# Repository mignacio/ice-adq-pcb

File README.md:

# ice-adq-pcb

This printed circuit board is a Shield or Poncho for the EDU-CIAA board.
It is a datalogger for internal combustion engines, it has three digital thermocouple readout sensor.
One variable reluctance RPM sensor.
One Narrowband Lambda probe analog interface.
And a resistive oil pressure sensor analog interface.
It trasmits data over bluetooth via an HM-10 BLE module.

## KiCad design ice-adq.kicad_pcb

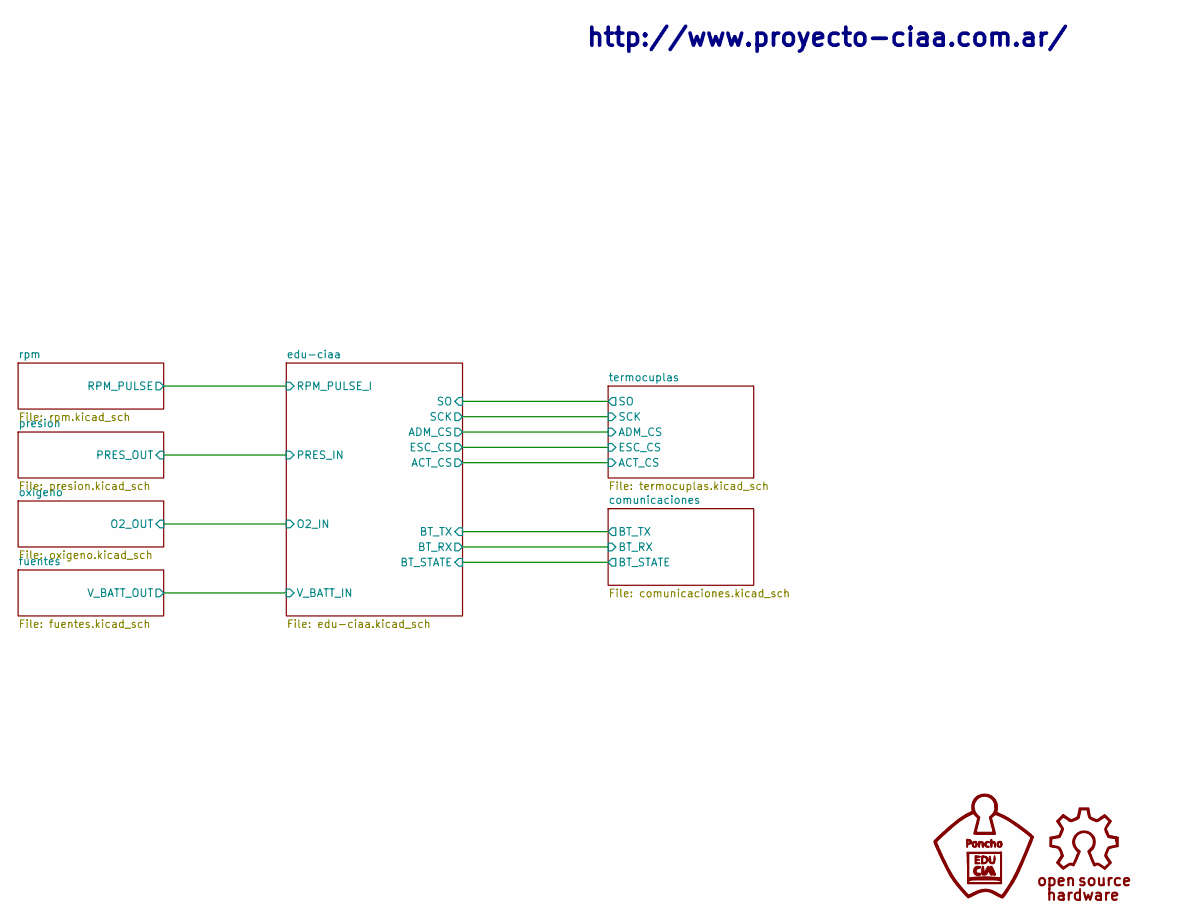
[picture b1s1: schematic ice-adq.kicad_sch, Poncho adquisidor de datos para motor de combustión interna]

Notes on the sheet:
http://www.proyecto-ciaa.com.ar/

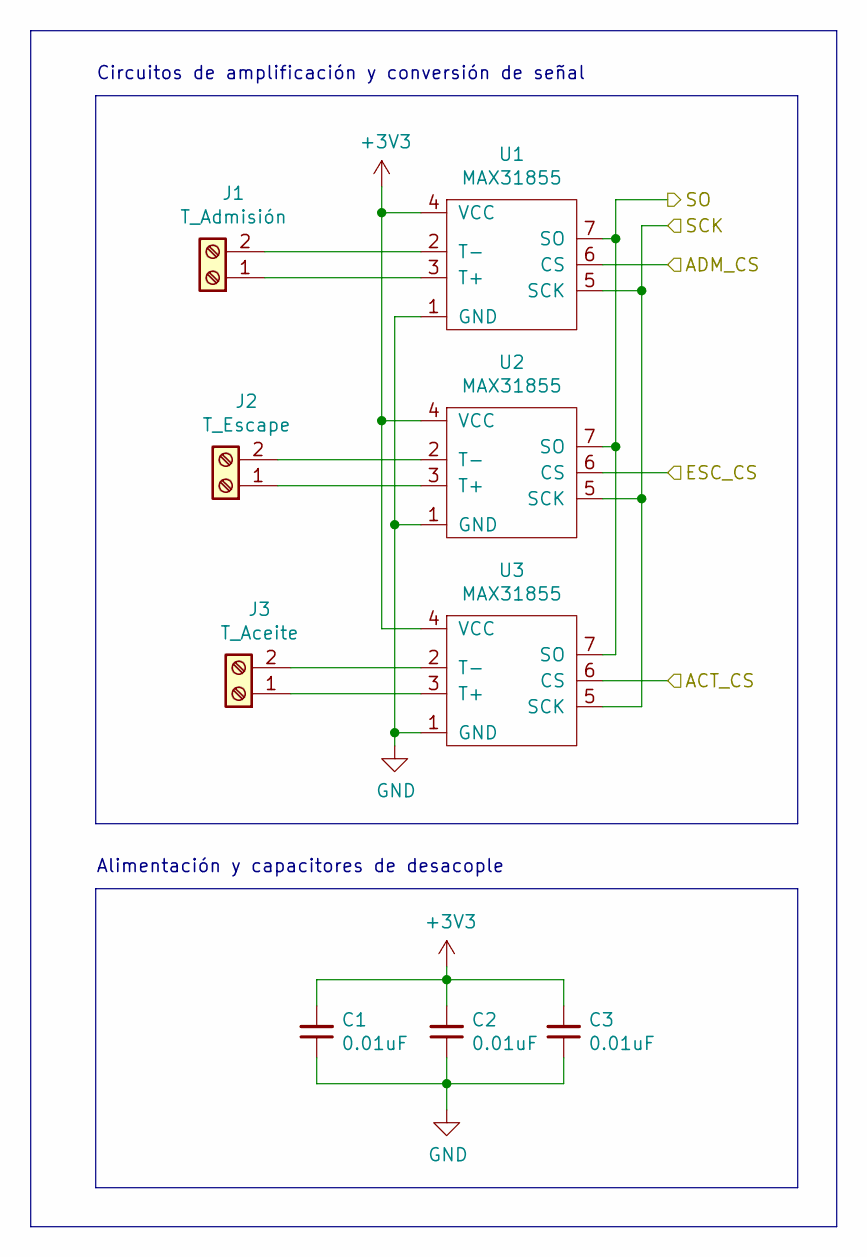
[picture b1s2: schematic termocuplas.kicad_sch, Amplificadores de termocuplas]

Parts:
C1, C2, C3: 0.01uF; C_0805_2012Metric_Pad1.15x1.40mm_HandSolder
J1: T_Admisión; TerminalBlock_bornier-2_P5.08mm
J2: T_Escape; TerminalBlock_bornier-2_P5.08mm
J3: T_Aceite; TerminalBlock_bornier-2_P5.08mm
U1, U2, U3: MAX31855; SOIC-8_3.9x4.9mm_P1.27mm

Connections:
/edu-ciaa/ACT_CS: U3.6 (CS); also elsewhere on the board
/edu-ciaa/ADM_CS: U1.6 (CS); also elsewhere on the board
/edu-ciaa/ESC_CS: U2.6 (CS); also elsewhere on the board
/edu-ciaa/SCK: U1.5 (SCK), U2.5 (SCK), U3.5 (SCK); also elsewhere on the board
/edu-ciaa/SO: U1.7 (SO), U2.7 (SO), U3.7 (SO); also elsewhere on the board
GND: C1.1, C2.1, C3.1, U1.1 (GND), U2.1 (GND), U3.1 (GND); also elsewhere on the board
unnamed: J1.1, U1.3 (T+)
unnamed: J1.2, U1.2 (T-)
unnamed: J2.1, U2.3 (T+)
unnamed: J2.2, U2.2 (T-)
unnamed: J3.1, U3.3 (T+)
unnamed: J3.2, U3.2 (T-)

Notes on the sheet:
Circuitos de amplificación y conversión de señal
Alimentación y capacitores de desacople

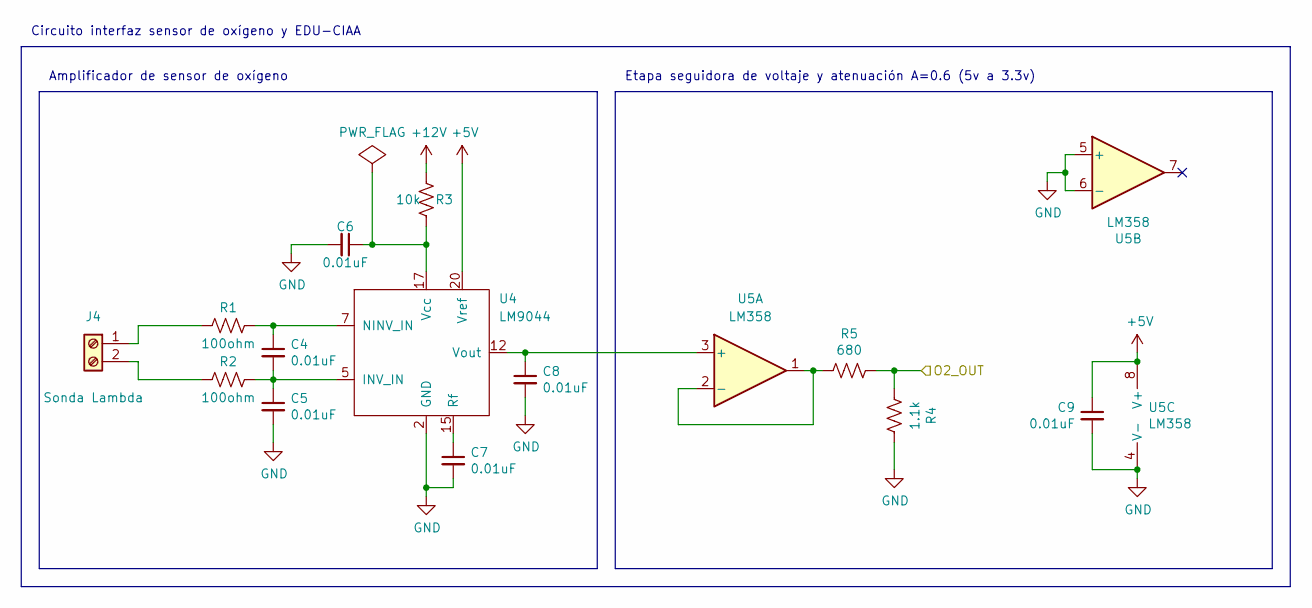
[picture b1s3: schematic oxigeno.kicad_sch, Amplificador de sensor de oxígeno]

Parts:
C4, C5, C6, C7, C8, C9: 0.01uF; C_0805_2012Metric_Pad1.15x1.40mm_HandSolder
J4: Sonda Lambda; TerminalBlock_bornier-2_P5.08mm
R1, R2: 100ohm; R_0805_2012Metric_Pad1.15x1.40mm_HandSolder
R3: 10k; R_0805_2012Metric_Pad1.15x1.40mm_HandSolder
R4: 1.1k; R_0805_2012Metric_Pad1.15x1.40mm_HandSolder
R5: 680; R_0805_2012Metric_Pad1.15x1.40mm_HandSolder
U4: LM9044; PLCC-20
U5: LM358; SOIC-8_3.9x4.9mm_P1.27mm

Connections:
+5V: C9.1, U4.20 (Vref), U5.8 (V+); also elsewhere on the board
+12V: R3.2; also elsewhere on the board
/edu-ciaa/O2_IN: R4.2, R5.1; also elsewhere on the board
GND: C5.2, C6.2, C7.2, C8.2, C9.2, R4.1, U4.2 (GND), U5.4 (V-), U5.5 (+), U5.6 (-); also elsewhere on the board
unnamed: C4.1, R1.1, U4.7 (NINV_IN)
unnamed: C4.2, C5.1, R2.1, U4.5 (INV_IN)
unnamed: C6.1, R3.1, U4.17 (Vcc)
unnamed: C7.1, U4.15 (Rf)
unnamed: C8.1, U4.12 (Vout), U5.3 (+)
unnamed: J4.1, R1.2
unnamed: J4.2, R2.2
unnamed: R5.2, U5.1, U5.2 (-)

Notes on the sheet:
Etapa seguidora de voltaje y atenuación A=0.6 (5v a 3.3v)
Amplificador de sensor de oxígeno
Circuito interfaz sensor de oxígeno y EDU-CIAA

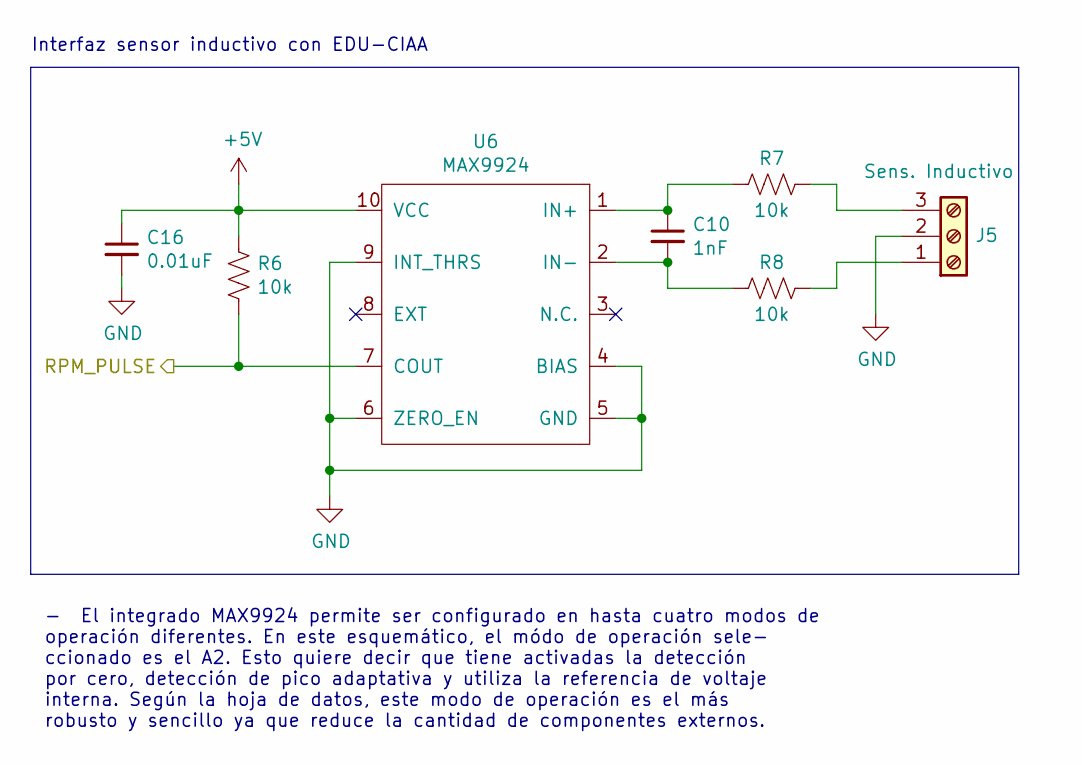
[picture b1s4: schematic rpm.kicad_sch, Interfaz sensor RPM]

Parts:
C10: 1nF; C_0805_2012Metric_Pad1.15x1.40mm_HandSolder
C16: 0.01uF; C_0805_2012Metric_Pad1.15x1.40mm_HandSolder
J5: Sens. Inductivo; TerminalBlock_bornier-3_P5.08mm
R6, R7, R8: 10k; R_0805_2012Metric_Pad1.15x1.40mm_HandSolder
U6: MAX9924; UMAX10

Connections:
+5V: C16.1, R6.1, U6.10 (VCC); also elsewhere on the board
/rpm/RPM_PULSE: R6.2, U6.7 (COUT); also elsewhere on the board
GND: C16.2, J5.2, U6.4 (BIAS), U6.5 (GND), U6.6 (ZERO_EN), U6.9 (INT_THRS); also elsewhere on the board
unnamed: C10.1, R7.2, U6.1 (IN+)
unnamed: C10.2, R8.2, U6.2 (IN-)
unnamed: J5.1, R8.1
unnamed: J5.3, R7.1

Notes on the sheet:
- El integrado MAX9924 permite ser configurado en hasta cuatro modos de operación diferentes. En este esquemático, el módo de operación sele- ccionado es el A2. Esto quiere decir que tiene activadas la detección por cero, detección de pico adaptativa y utiliza la referencia de voltaje interna. Segú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
Interfaz sensor inductivo con EDU-CIAA

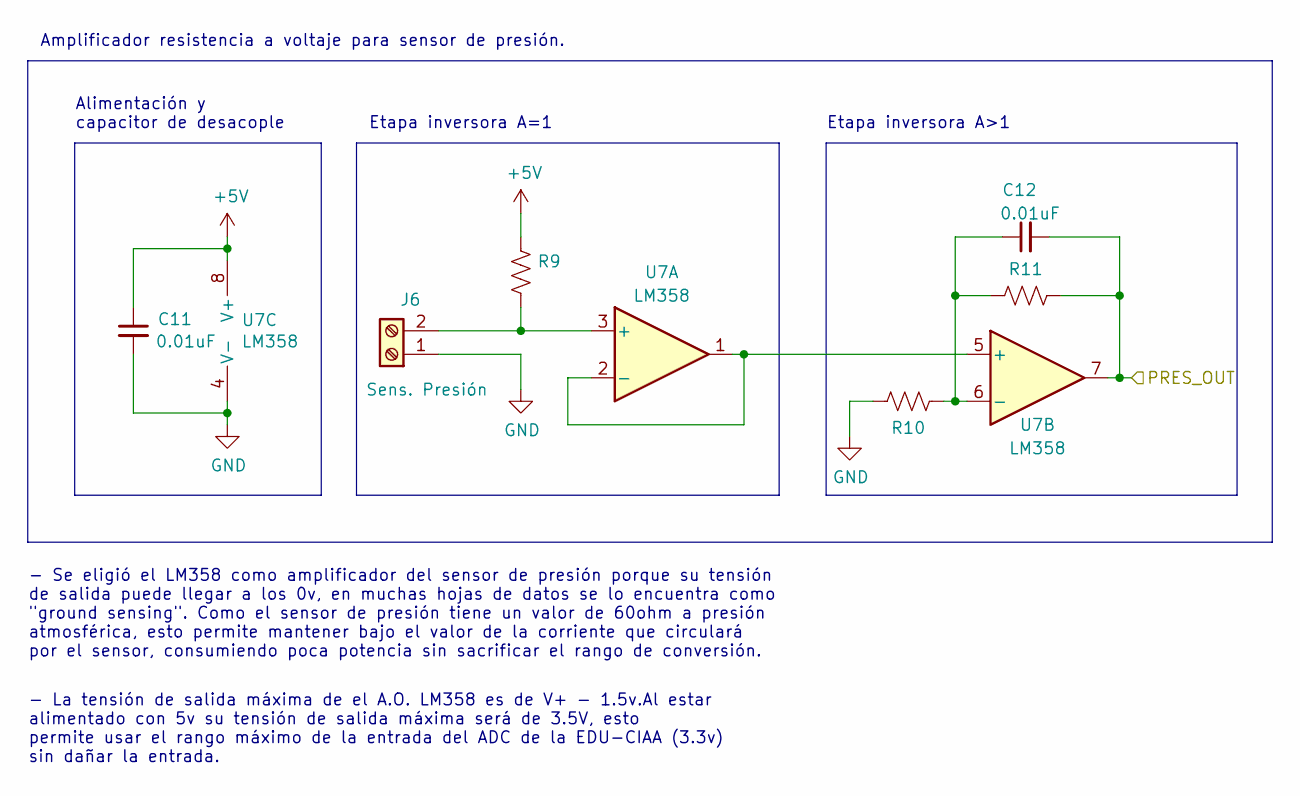
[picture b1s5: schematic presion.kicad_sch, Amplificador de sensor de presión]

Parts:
C11, C12: 0.01uF; C_0805_2012Metric_Pad1.15x1.40mm_HandSolder
J6: Sens. Presión; TerminalBlock_bornier-2_P5.08mm
R9, R10, R11: R_US; R_0805_2012Metric_Pad1.15x1.40mm_HandSolder
U7: LM358; SOIC-8_3.9x4.9mm_P1.27mm

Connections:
+5V: C11.1, R9.1, U7.8 (V+); also elsewhere on the board
/edu-ciaa/PRES_IN: C12.2, R11.1, U7.7; also elsewhere on the board
GND: C11.2, J6.1, R10.1, U7.4 (V-); also elsewhere on the board
unnamed: C12.1, R10.2, R11.2, U7.6 (-)
unnamed: J6.2, R9.2, U7.3 (+)
unnamed: U7.1, U7.2 (-), U7.5 (+)

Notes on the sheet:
Etapa inversora A>1
Amplificador resistencia a voltaje para sensor de presión.
Etapa inversora A=1
- Se eligió el LM358 como amplificador del sensor de presión porque su tensión de salida puede llegar a los 0v, en muchas hojas de datos se lo encuentra como "ground sensing". Como el sensor de presión tiene un valor de 60ohm a presión atmosférica, esto permite mantener bajo el valor de la corrient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
- La tensión de salida máxima de el A.O. LM358 es de V+ - 1.5v.Al estar alimentado con 5v su tensión de salida máxima será de 3.5V, esto permite usar el rango máximo de la entrada del ADC de la EDU-CIAA (3.3v) sin dañar la entrada.
Alimentación y capacitor de desacople

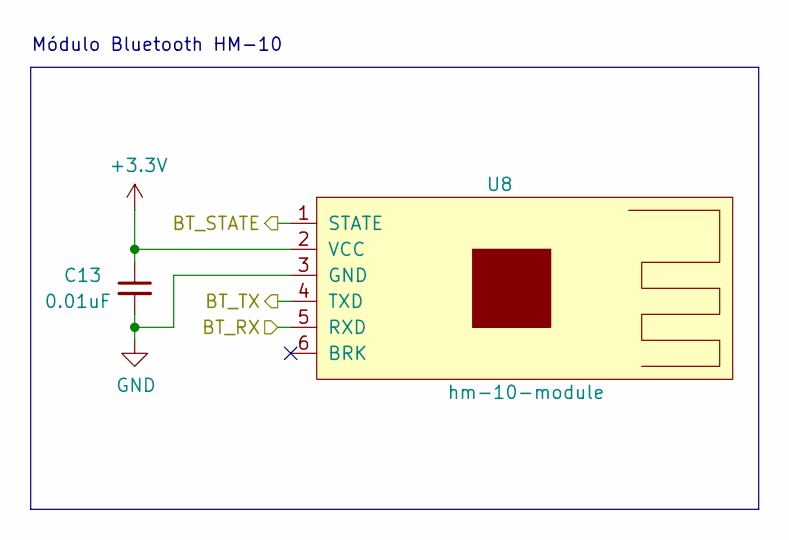
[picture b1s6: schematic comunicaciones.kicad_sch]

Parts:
C13: 0.01uF; C_0805_2012Metric_Pad1.15x1.40mm_HandSolder
U8: hm-10-module

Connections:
/comunicaciones/BT_RX: U8.5 (RXD); also elsewhere on the board
/comunicaciones/BT_STATE: U8.1 (STATE); also elsewhere on the board
/comunicaciones/BT_TX: U8.4 (TXD); also elsewhere on the board
GND: C13.2, U8.3 (GND); also elsewhere on the board

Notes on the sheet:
Módulo Bluetooth HM-10

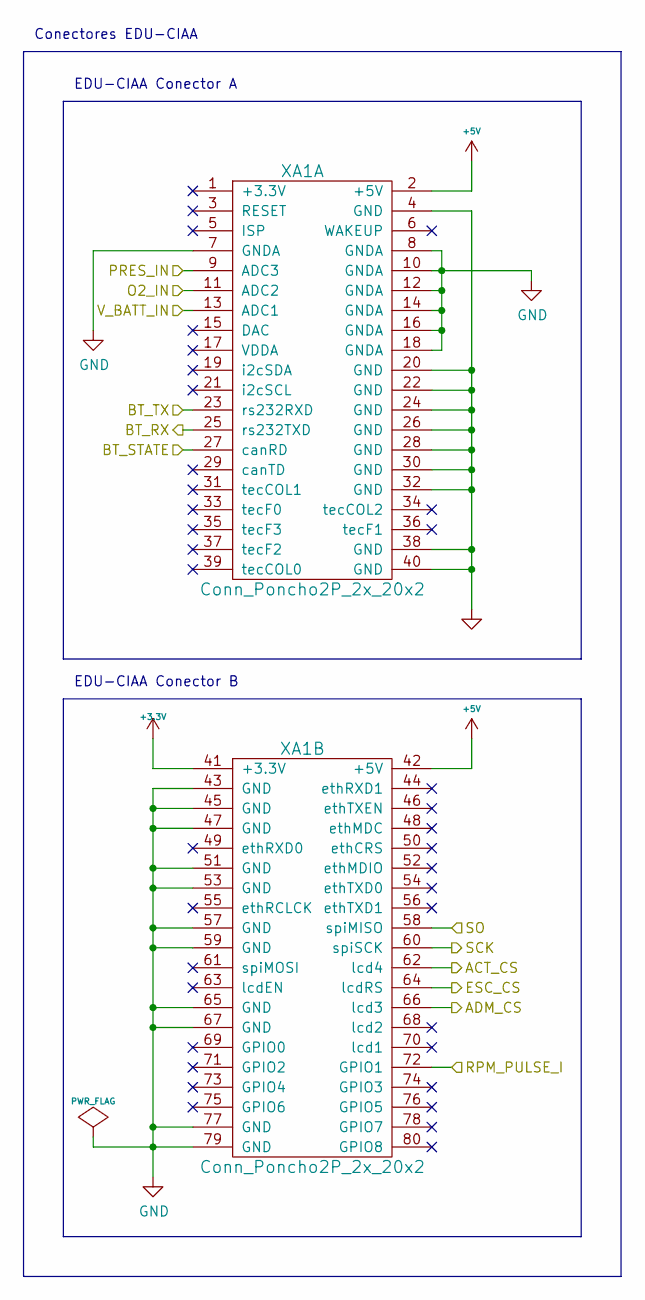
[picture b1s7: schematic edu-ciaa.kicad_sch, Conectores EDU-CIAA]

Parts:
XA1: Conn_Poncho2P_2x_20x2; Conn_Poncho_SinBorde; Digikey# 952-1387-ND

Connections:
+5V: XA1.2 (+5V), XA1.42 (+5V); also elsewhere on the board
/comunicaciones/BT_RX: XA1.25 (rs232TXD); also elsewhere on the board
/comunicaciones/BT_STATE: XA1.27 (canRD); also elsewhere on the board
/comunicaciones/BT_TX: XA1.23 (rs232RXD); also elsewhere on the board
/edu-ciaa/ACT_CS: XA1.62 (lcd4); also elsewhere on the board
/edu-ciaa/ADM_CS: XA1.66 (lcd3); also elsewhere on the board
/edu-ciaa/ESC_CS: XA1.64 (lcdRS); also elsewhere on the board
/edu-ciaa/O2_IN: XA1.11 (ADC2); also elsewhere on the board
/edu-ciaa/PRES_IN: XA1.9 (ADC3); also elsewhere on the board
/edu-ciaa/SCK: XA1.60 (spiSCK); also elsewhere on the board
/edu-ciaa/SO: XA1.58 (spiMISO); also elsewhere on the board
/edu-ciaa/V_BATT_IN: XA1.13 (ADC1); also elsewhere on the board
/rpm/RPM_PULSE: XA1.72 (GPIO1); also elsewhere on the board
GND: XA1.4 (GND), XA1.7 (GNDA), XA1.8 (GNDA), XA1.10 (GNDA), XA1.12 (GNDA), XA1.14 (GNDA), XA1.16 (GNDA), XA1.18 (GNDA), XA1.20 (GND), XA1.22 (GND), XA1.24 (GND), XA1.26 (GND), XA1.28 (GND), XA1.30 (GND), XA1.32 (GND), XA1.38 (GND), XA1.40 (GND), XA1.43 (GND), XA1.45 (GND), XA1.47 (GND), XA1.51 (GND), XA1.53 (GND), XA1.57 (GND), XA1.59 (GND), XA1.65 (GND), XA1.67 (GND), XA1.77 (GND), XA1.79 (GND); also elsewhere on the board

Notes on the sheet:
EDU-CIAA Conector A
EDU-CIAA Conector B
Conectores EDU-CIAA

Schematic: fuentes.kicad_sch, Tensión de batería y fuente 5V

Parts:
C14: 0.22uF; C_0805_2012Metric_Pad1.15x1.40mm_HandSolder
C15, C17, C18: 0.01uF; C_0805_2012Metric_Pad1.15x1.40mm_HandSolder
J7: BATT; TerminalBlock_bornier-2_P5.08mm
R12: 39k; R_0805_2012Metric_Pad1.15x1.40mm_HandSolder
R13: 10k; R_0805_2012Metric_Pad1.15x1.40mm_HandSolder
U9: L7805; TO-263-3_TabPin2
U10: LM358; SOIC-8_3.9x4.9mm_P1.27mm

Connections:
+5V: C15.1, C17.1, U9.3 (OUT), U10.8 (V+); also elsewhere on the board
+12V: C14.1, J7.1, R12.1, U9.1 (IN); also elsewhere on the board
/edu-ciaa/V_BATT_IN: U10.1, U10.2 (-); also elsewhere on the board
GND: C14.2, C15.2, C17.2, C18.2, J7.2, R13.2, U9.2 (GND), U10.4 (V-), U10.5 (+), U10.6 (-); also elsewhere on the board
unnamed: C18.1, R12.2, R13.1, U10.3 (+)

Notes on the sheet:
Conector batería y fuente 5 voltios.
Interfaz tensión de batería y ADC

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
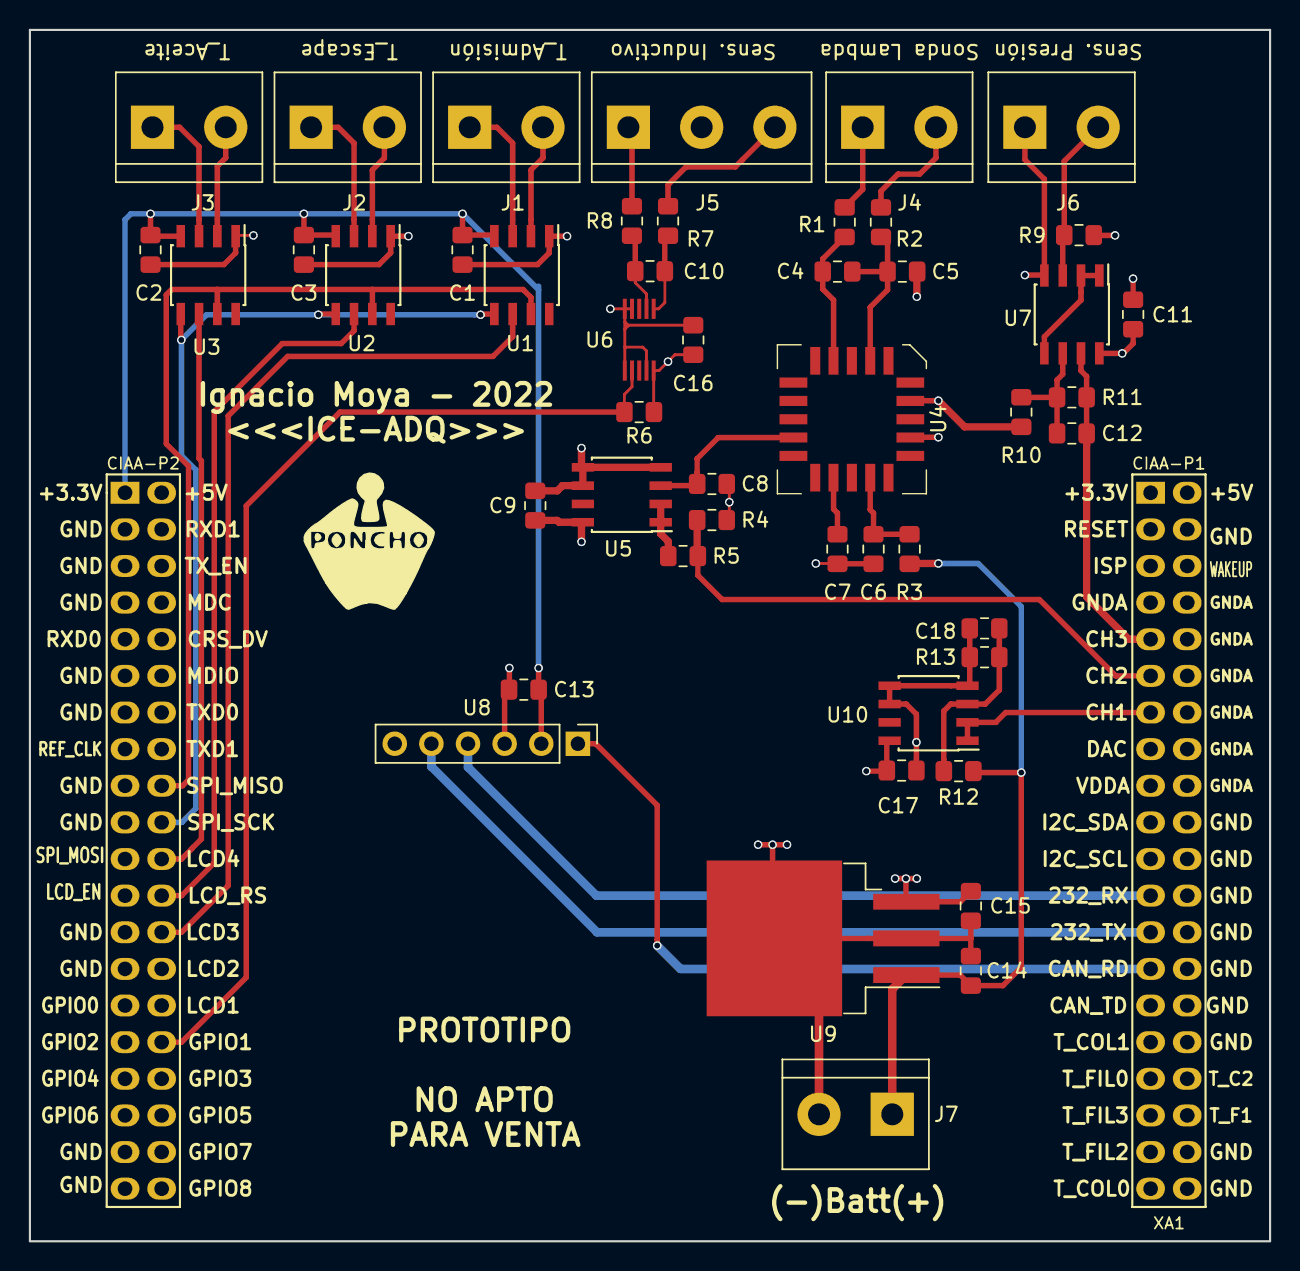
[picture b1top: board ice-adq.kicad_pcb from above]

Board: 4 copper layers, 86.0 x 84.0 mm, 49 parts (0 on the bottom side), 38 nets.

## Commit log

2021-01-11 segundo commit
2021-02-07 Terminado el esquemático para los amplificadores de termocuplas
2021-02-13 avances en el esquematico del amplificador de sonda lambda
2021-12-11 Primer rev esquematicos RPM y comunicaciones
2021-12-18 Esquematicos mayormente terminados, falta sub-hoja edu ciaa, fuentes de alimentacion y poner valores a los componentes
2021-12-18 Se agrego esquematico de fuentes y se corrigieron errores de ERC
2021-12-19 Correccion de errores y se designaron huellas a casi todos los componentes
2021-12-19 Ubicación de componentes y algo de ruteado
2021-12-29 Se cambio pack de 7805 y de 9044
2022-01-02 Ruteado de circuito de medicion de bateria
2022-01-02 Se agregaron modelos 3d faltantes
2023-03-05 Comitee cambios que estaban hechos.
2023-03-05 Migración a kicad 7.0.
2023-04-08 Actualizacion a kicad 7, seleccion de ganancia de la etapa de amplificacion de presion de aceite.
2023-04-08 Cambios en plano de presion y agregue render en 3D de la placa.
2023-04-08 Agregue un readme y render 3D de la placa.
2023-04-15 Agregué datos sobre función transferencia del circuito de presión.
